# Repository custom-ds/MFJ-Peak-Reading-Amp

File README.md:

# MFJ-Peak-Reading-Amp
Amplifier to convert an MFJ dual-needle meter to display peak RF power.

## Circuit Theory

## Installation

## Credits

The circuit design originally came from Jeff Smith, VE1ZAC on his post regarding the modifications to the MFJ-998 Legal Limit Tuner. More details can be found at https://ve1zac.com/My%20MFJ.htm.

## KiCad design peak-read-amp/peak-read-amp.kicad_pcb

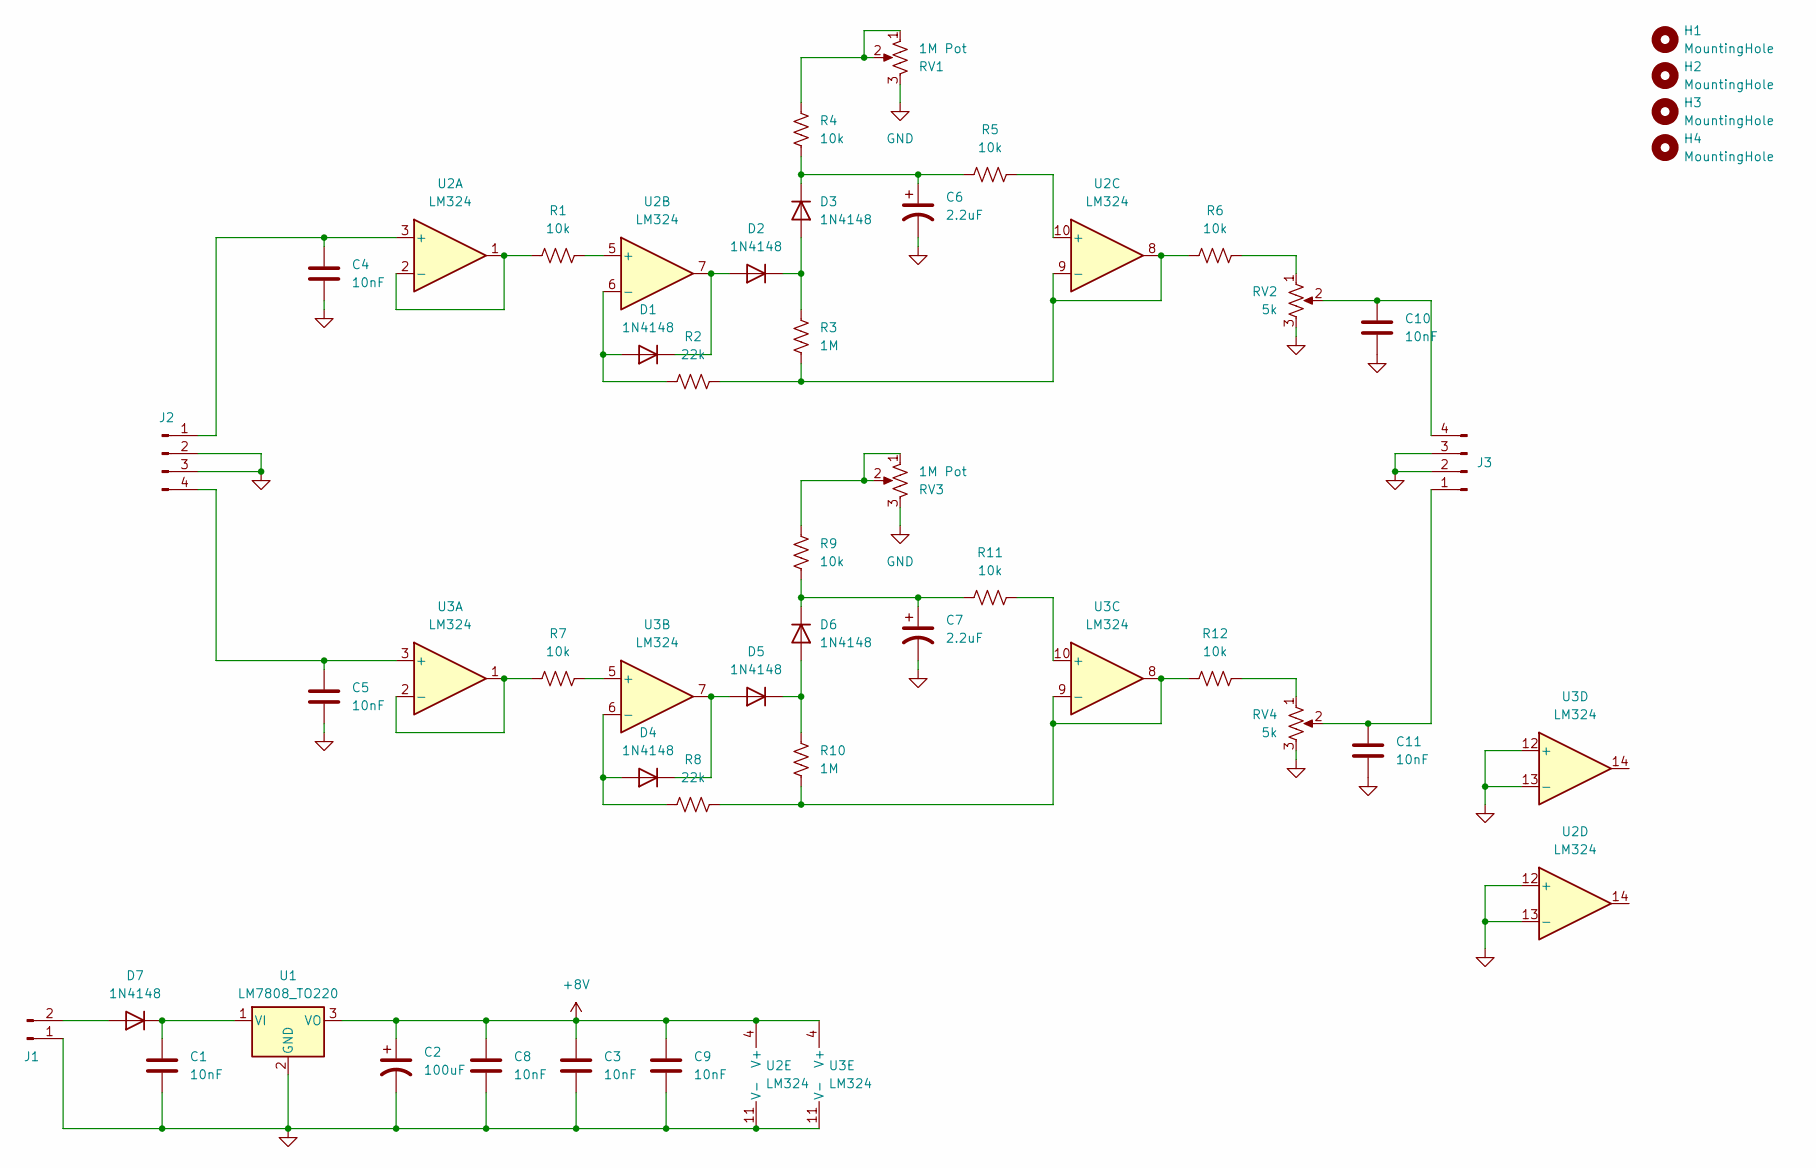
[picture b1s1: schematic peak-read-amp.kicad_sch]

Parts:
C1, C3, C4, C5, C8, C9, C10, C11: 10nF; C_0805_2012Metric; Digikey 399-1158-1-ND
C2: 100uF; CP_Radial_D10.0mm_P5.00mm; Digikey P19602CT-ND
C6, C7: 2.2uF; C_0805_2012Metric; Digikey 445-1420-2-ND
D1, D2, D3, D4, D5, D6, D7: 1N4148; D_SOD-123; Digikey 1N4148W-FDITR-ND
H1, H2, H3, H4: MountingHole; MountingHole_2.7mm_M2.5
J1: Conn_01x02_Pin; PinHeader_1x02_P2.54mm_Horizontal; Digikey WM4300-ND, WM2000-ND, WM2200-ND
J2, J3: Conn_01x04_Pin; PinHeader_1x04_P2.54mm_Horizontal; Digikey WM4302-ND, WM2002-ND, WM2200-ND
R1, R4, R5, R6, R7, R9, R11, R12: 10k; R_0805_2012Metric; Digikey 311-10KARCT-ND
R2, R8: 22k; R_0805_2012Metric; Digikey 311-22KARCT-ND
R3, R10: 1M; R_0805_2012Metric; Digikey 311-1.0MARCT-ND
RV1, RV3: 1M Pot; Potentiometer_Bourns_3339W_Horizontal; Digikey 3386H-1-105LF
RV2, RV4: 5k; Potentiometer_Bourns_3339W_Horizontal; Digikey 3386H-502LF-ND
U1: LM7808_TO220; TO-252-3_TabPin2; Digikey BA7808FP-E2TR-ND
U2, U3: LM324; SOIC-14_3.9x8.7mm_P1.27mm; Digikey 296-14597-2-ND

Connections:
+8V: C2.1, C3.1, C8.1, C9.1, U1.3 (VO), U2.4 (V+), U3.4 (V+)
GND: C1.2, C2.2, C3.2, C4.2, C5.2, C6.2, C7.2, C8.2, C9.2, C10.2, C11.2, J1.1, J2.2, J2.3, J3.2, J3.3, RV1.3, RV2.3, RV3.3, RV4.3, U1.2 (GND), U2.11 (V-), U2.12 (+), U2.13 (-), U3.11 (V-), U3.12 (+), U3.13 (-)
unnamed: D1.2 (A), R2.1, U2.6 (-)
unnamed: D1.1 (K), D2.2 (A), U2.7
unnamed: D2.1 (K), D3.2 (A), R3.2
unnamed: C6.1, D3.1 (K), R4.1, R5.2
unnamed: D4.2 (A), R8.1, U3.6 (-)
unnamed: D4.1 (K), D5.2 (A), U3.7
unnamed: D5.1 (K), D6.2 (A), R10.2
unnamed: C7.1, D6.1 (K), R9.1, R11.2
unnamed: D7.2 (A), J1.2
unnamed: C1.1, D7.1 (K), U1.1 (VI)
unnamed: C4.1, J2.1, U2.3 (+)
unnamed: C5.1, J2.4, U3.3 (+)
unnamed: C11.1, J3.1, RV4.2
unnamed: C10.1, J3.4, RV2.2
unnamed: R4.2, RV1.1, RV1.2
unnamed: R6.1, RV2.1
unnamed: R9.2, RV3.1, RV3.2
unnamed: R12.1, RV4.1
unnamed: R1.1, U2.1, U2.2 (-)
unnamed: R1.2, U2.5 (+)
unnamed: R5.1, U2.10 (+)
unnamed: R2.2, R3.1, R6.2, U2.8, U2.9 (-)
unnamed: R7.1, U3.1, U3.2 (-)
unnamed: R7.2, U3.5 (+)
unnamed: R11.1, U3.10 (+)
unnamed: R8.2, R10.1, R12.2, U3.8, U3.9 (-)

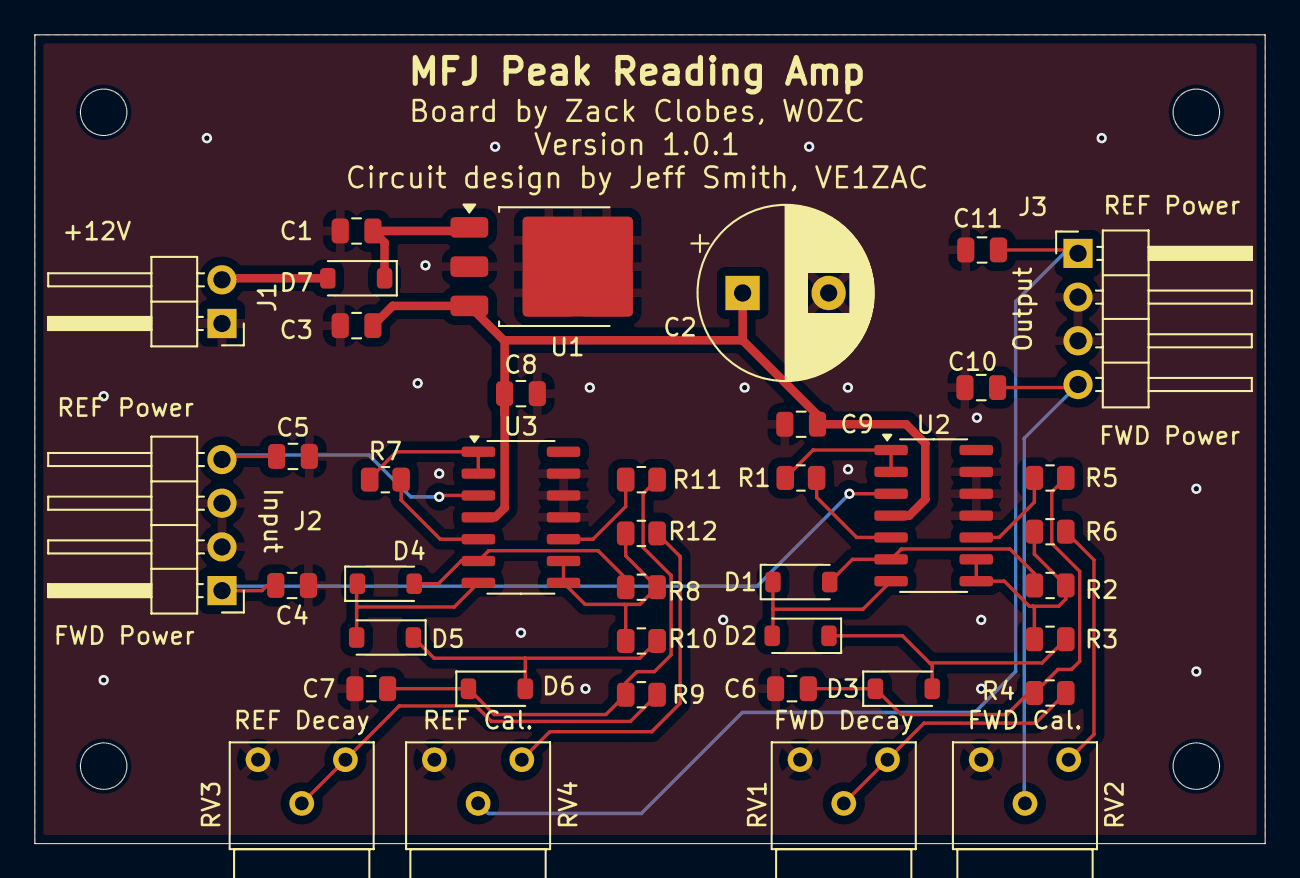
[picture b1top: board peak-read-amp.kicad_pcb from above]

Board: 2 copper layers, 71.5 x 47.0 mm, 44 parts (0 on the bottom side), 28 nets.

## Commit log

2025-03-02 PCB version 1.0.1 to add mounting holes and clean up a few minor inconsistencies. Upgraded to Kicad v9.
